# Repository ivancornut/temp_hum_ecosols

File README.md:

# Accurate microclimate measures
The aim of this project is to build an accurate air temperature and humidity sensor for environmental science. We will be using the SHT45 sensor from sensirion since it presents the right accuracy, precicison and drift for the job. Due to its use outdoors we will use the version equipped with a PTFE filter membrane. 

## Hardware

### Electronics

#### Bill of materials
- 2 10kOhm 1206 resistors (0.109€ - bought [here](https://fr.rs-online.com/web/p/resistances-a-montage-en-surface/6791765))
- 1 100nF 1206 capacitor (0.05€ - bought [here](https://fr.rs-online.com/web/p/condensateurs-ceramique-multicouches/1335654))
- 1 SHT45-AD1F-R2 sensirion sensor (3.07 € - bought [here](https://www.mouser.fr/ProductDetail/403-SHT45-AD1F-R2))
- 50 PCBs and 1 stencil (70€ - PCBway)

#### Cost per sensor
The cost of the sensor board is 5€. Time to apply solder paste and reflow is around 20min. So considering somebody paid 60€ an hour this amounts to 25€ per sensor. 

### Microclimate radiation shield

#### Design
To complement the sensor we have designed a small and discrete radiation shield that is optimised for 3D printing. This is to be used inside canopies to measure the local microclimate. It is designed in 3 parts and the bottom part has a well-adjuster holder for the PCB.
This piece should ideally be printed with UV resistant white PETG. We use the Nanovia PETG-GF-UV: [https://nanovia.tech/en/ref/nanovia-petg-gf-uv/](https://nanovia.tech/en/ref/nanovia-petg-gf-uv/)

#### Cost per shield
The material costs per shield are estimated at around 3€ if we consider that a 500g spool of this filament costs around 40€. 

## Final result

### Shield

### Front of the reflowed board

### Back of the reflowed board

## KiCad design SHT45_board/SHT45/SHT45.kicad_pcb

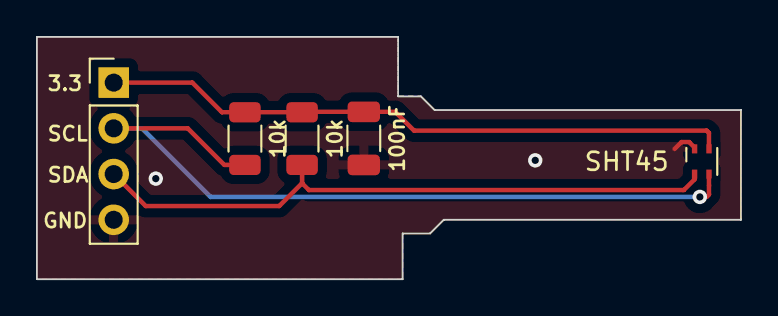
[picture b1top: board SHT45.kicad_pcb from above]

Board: 2 copper layers, 39.1 x 13.5 mm, 5 parts (0 on the bottom side), 4 nets.

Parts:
10k, 10k#2: 10k; R_1206_3216Metric
100nF: 100nF; C_1206_3216Metric
J1: Conn_01x04_Socket; PinHeader_1x04_P2.54mm_Vertical
SHT45: SHT4x; Sensirion_DFN-4_1.5x1.5mm_P0.8mm_SHT4x_NoCentralPad

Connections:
+3.3V: 10k.1, 10k#2.1, 100nF.1, J1.1, SHT45.3 (VDD)
/SCL: 10k.2, J1.2, SHT45.2 (SCL)
/SDA: 10k#2.2, J1.3, SHT45.1 (SDA)
GND: 100nF.2, J1.4, SHT45.4 (VSS)

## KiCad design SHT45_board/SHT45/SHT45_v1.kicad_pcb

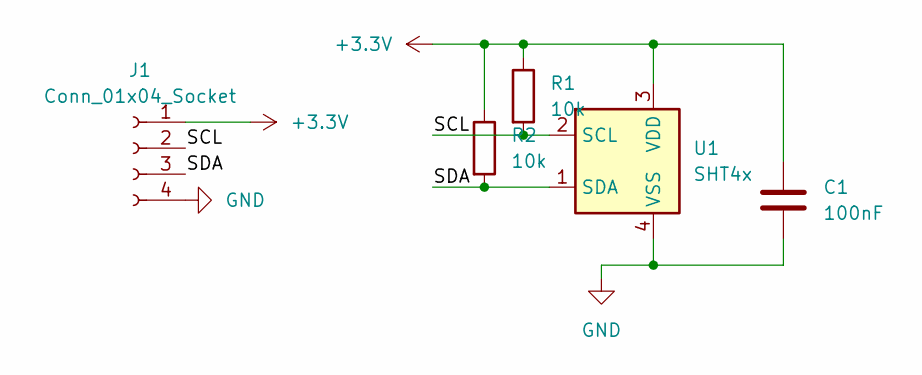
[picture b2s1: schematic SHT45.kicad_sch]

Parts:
C1: 100nF; C_1206_3216Metric
J1: Conn_01x04_Socket; PinHeader_1x04_P2.54mm_Vertical
R1, R2: 10k; R_1206_3216Metric
U1: SHT4x; Sensirion_DFN-4_1.5x1.5mm_P0.8mm_SHT4x_NoCentralPad

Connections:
+3.3V: C1.1, J1.1, R1.1, R2.1, U1.3 (VDD)
/SCL: J1.2, R1.2, U1.2 (SCL)
/SDA: J1.3, R2.2, U1.1 (SDA)
GND: C1.2, J1.4, U1.4 (VSS)

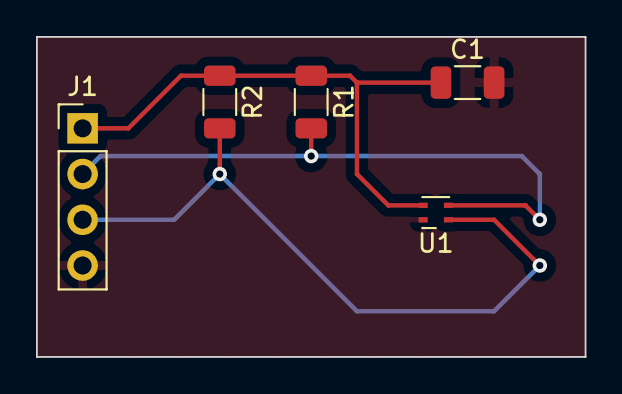
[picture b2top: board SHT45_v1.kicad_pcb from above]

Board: 2 copper layers, 30.5 x 17.8 mm, 5 parts (0 on the bottom side), 4 nets.

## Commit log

2023-08-28 Creation of the repository
2023-08-28 Sensor board image
2023-08-30 PCB imgage
2023-10-25 Update read me
    Test Git
2024-05-21 Added stls for radiation shroud
2024-05-24 Update of Stls
2024-05-24 Addition of mesh picture
2024-05-25 add Pictures
